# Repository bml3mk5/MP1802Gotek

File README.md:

# VFOインターフェース for MP-1802 / MP-1870 on 日立ベーシックマスターレベル３ / MB-S1

## フォルダ構成

    Board/ ......................... 基板設計(KiCAD Version 6)

-----
# VFO Interface for MP-1802 / MP-1870 on HITACH BASIC MASTER LEVEL3 / MB-S1

## Folders:

    Board/ ......................... Circuit board design(KiCAD Version 6)

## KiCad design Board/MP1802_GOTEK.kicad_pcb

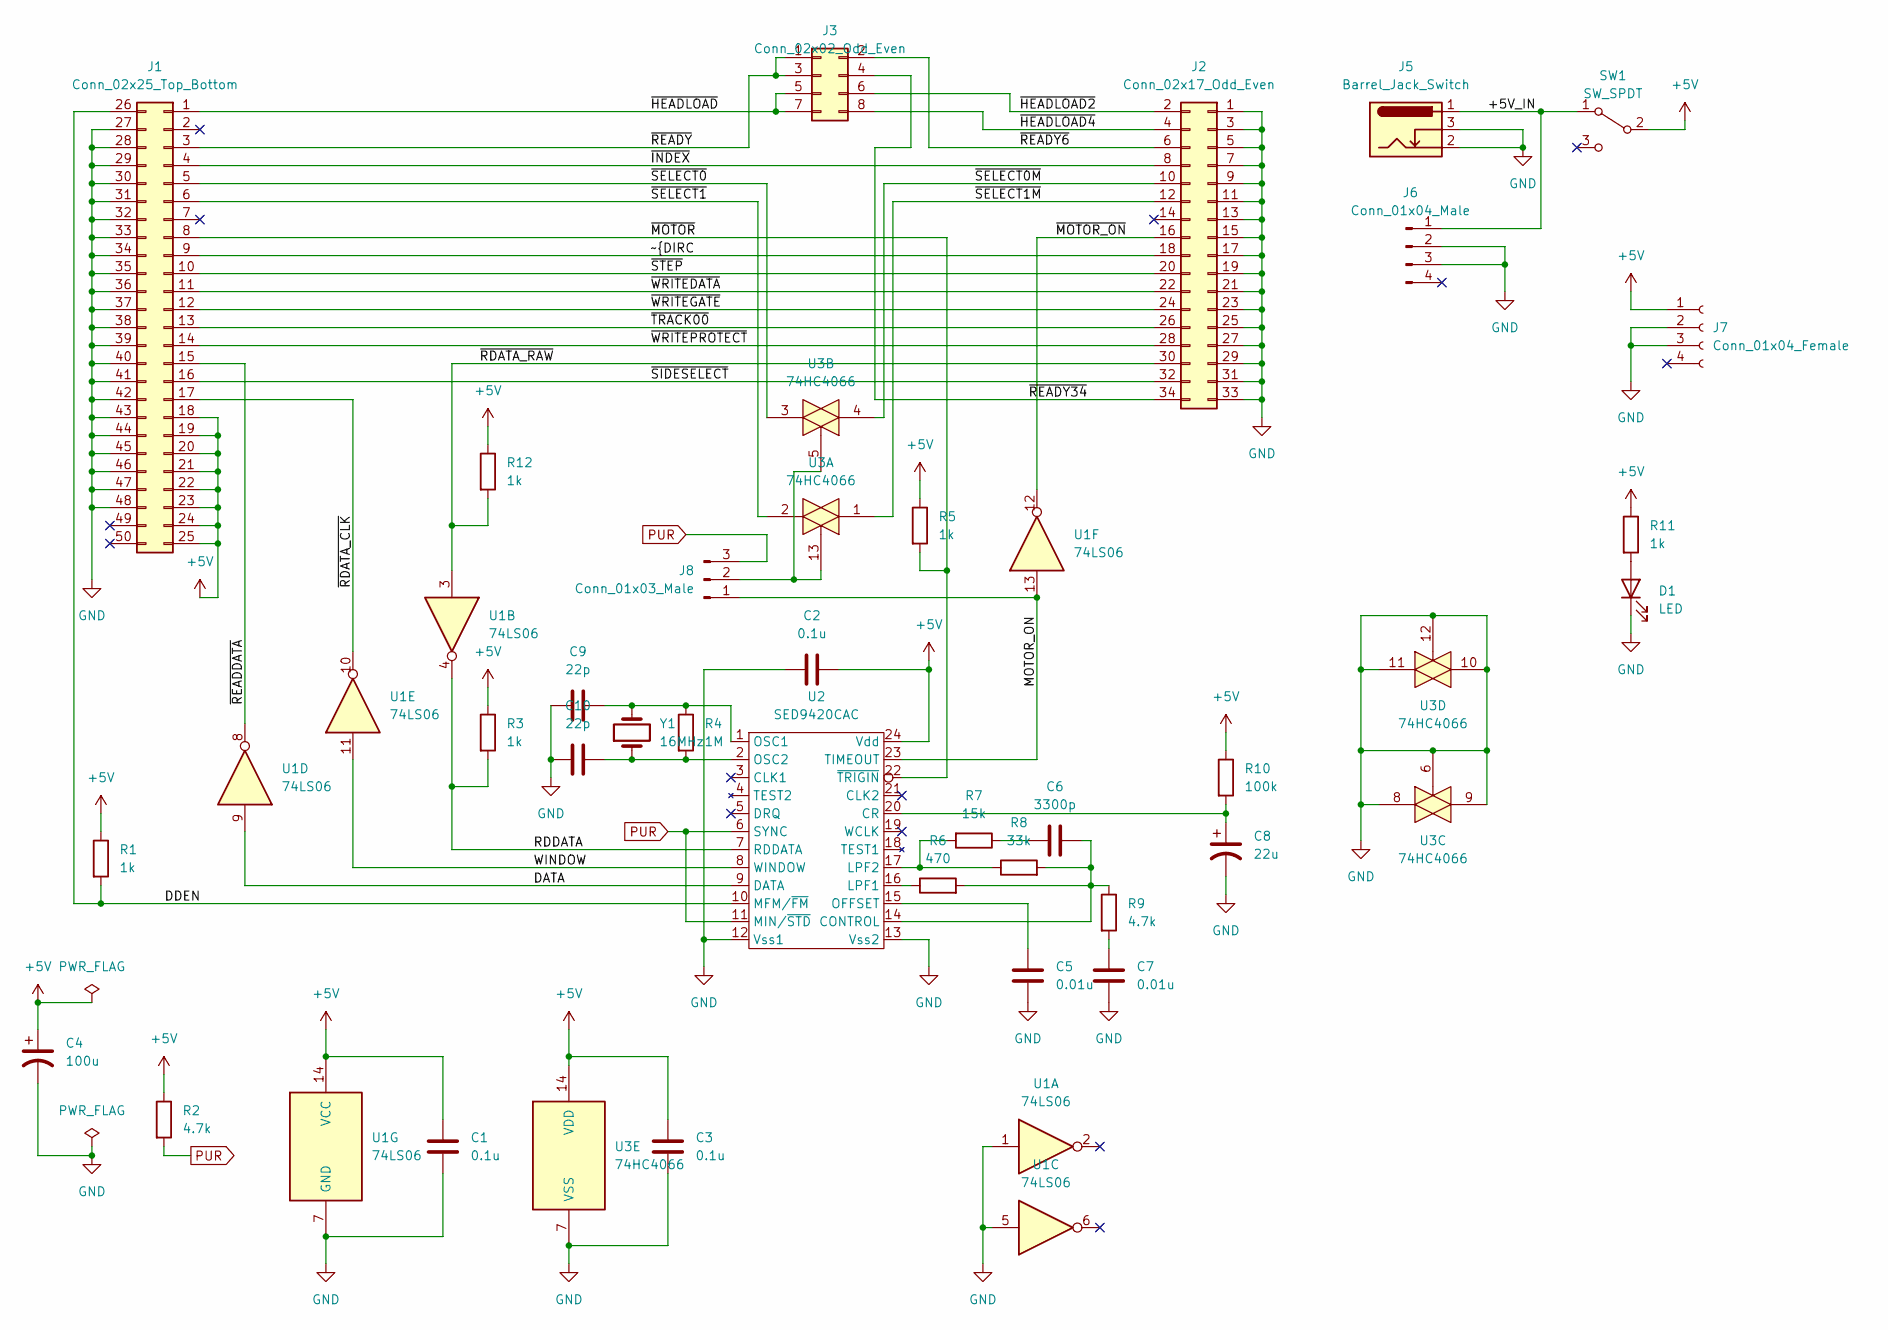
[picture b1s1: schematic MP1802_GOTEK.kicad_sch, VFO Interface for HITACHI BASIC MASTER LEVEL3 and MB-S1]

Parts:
C1, C2, C3: 0.1u; C_Disc_D3.0mm_W2.0mm_P2.50mm
C4: 100u; CP_Radial_D6.3mm_P2.50mm
C5, C7: 0.01u; C_Disc_D3.0mm_W2.0mm_P2.50mm
C6: 3300p; C_Disc_D3.0mm_W2.0mm_P2.50mm
C8: 22u; CP_Radial_D6.3mm_P2.50mm
C9, C10: 22p; C_Disc_D3.0mm_W2.0mm_P2.50mm
D1: LED; LED_D3.0mm
J1: Conn_02x25_Top_Bottom; YA_PinHeader_2x25_P2.54mm_Vertical
J2: Conn_02x17_Odd_Even; YA_PinHeader_2x17_P2.54mm_Vertical
J3: Conn_02x02_Odd_Even; PinHeader_2x04_P2.54mm_Vertical
J5: Barrel_Jack_Switch; YA_BarrelJack_CUI_PJ-102AH_Horizontal
J6: Conn_01x04_Male; PinHeader_1x04_P2.54mm_Horizontal
J7: Conn_01x04_Female; PinSocket_1x04_P2.54mm_Vertical
J8: Conn_01x03_Male; PinHeader_1x03_P2.54mm_Vertical
R1, R3, R5, R11, R12: 1k; R_Axial_DIN0207_L6.3mm_D2.5mm_P2.54mm_Vertical
R2: 4.7k; R_Axial_DIN0207_L6.3mm_D2.5mm_P2.54mm_Vertical
R4: 1M; R_Axial_DIN0207_L6.3mm_D2.5mm_P2.54mm_Vertical
R6: 470; R_Axial_DIN0207_L6.3mm_D2.5mm_P7.62mm_Horizontal
R7: 15k; R_Axial_DIN0207_L6.3mm_D2.5mm_P7.62mm_Horizontal
R8: 33k; R_Axial_DIN0207_L6.3mm_D2.5mm_P7.62mm_Horizontal
R9: 4.7k; R_Axial_DIN0207_L6.3mm_D2.5mm_P7.62mm_Horizontal
R10: 100k; R_Axial_DIN0207_L6.3mm_D2.5mm_P2.54mm_Vertical
SW1: SW_SPDT; SW_Switch_SS12D10_SPDT
U1: 74LS06; DIP-14_W7.62mm_Socket
U2: SED9420CAC; DIP-24_W15.24mm_Socket
U3: 74HC4066; DIP-14_W7.62mm_Socket
Y1: 16MHz; Crystal_HC18-U_Vertical

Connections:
+5V: C1.2, C2.2, C3.2, C4.1, J1.18, J1.19, J1.20, J1.21, J1.22, J1.23, J1.24, J1.25, J7.1, R1.1, R2.1, R3.1, R5.1, R10.1, R11.1, R12.1, SW1.2 (B), U1.14 (VCC), U2.24 (Vdd), U3.14 (VDD)
/+5V_IN: J5.1, J6.1, SW1.1 (A)
/DATA: U1.9, U2.9 (DATA)
/DDEN: J1.26, R1.2, U2.10 (MFM/~FM)
/MOTOR_ON: J8.1, U1.13, U2.23 (TIMEOUT)
/RDDATA: R3.2, U1.4, U2.7 (RDDATA)
/WINDOW: U1.11, U2.8 (WINDOW)
/~DIRC: J1.9, J2.18
/~HEADLOAD2: J2.2, J3.6
/~HEADLOAD4: J2.4, J3.8
/~HEADLOAD: J1.1, J3.5, J3.7
/~INDEX: J1.4, J2.8
/~MOTOR_ON: J2.16, U1.12
/~MOTOR: J1.8, R5.2, U2.22 (~TRIGIN)
/~RDATA_CLK: J1.17, U1.10
/~RDATA_RAW: J2.30, R12.2, U1.3
/~READDATA: J1.15, U1.8
/~READY6: J2.6, J3.2
/~READY34: J2.34, J3.4
/~READY: J1.3, J3.1, J3.3
/~SELECT0M: J2.10, U3.4
/~SELECT0: J1.5, U3.3
/~SELECT1M: J2.12, U3.1
/~SELECT1: J1.6, U3.2
/~SIDESELECT: J1.16, J2.32
/~STEP: J1.10, J2.20
/~TRACK00: J1.13, J2.26
/~WRITEDATA: J1.11, J2.22
/~WRITEGATE: J1.12, J2.24
/~WRITEPROTECT: J1.14, J2.28
GND: C1.1, C2.1, C3.1, C4.2, C5.1, C7.1, C8.2, C9.1, C10.1, D1.1 (K), J1.27, J1.28, J1.29, J1.30, J1.31, J1.32, J1.33, J1.34, J1.35, J1.36, J1.37, J1.38, J1.39, J1.40, J1.41, J1.42, J1.43, J1.44, J1.45, J1.46, J1.47, J1.48, J2.1, J2.3, J2.5, J2.7, J2.9, J2.11, J2.13, J2.15, J2.17, J2.19, J2.21, J2.23, J2.25, J2.27, J2.29, J2.31, J2.33, J5.2, J5.3, J6.2, J6.3, J7.2, J7.3, U1.1, U1.5, U1.7 (GND), U2.12 (Vss1), U2.13 (Vss2), U3.6, U3.7 (VSS), U3.8, U3.9, U3.10, U3.11, U3.12
unnamed: C5.2, U2.15 (OFFSET)
unnamed: C6.1, R7.1
unnamed: C6.2, R6.2, R8.2, R9.1, U2.14 (CONTROL)
unnamed: C7.2, R9.2
unnamed: C8.1, R10.2, U2.20 (CR)
unnamed: C9.2, R4.1, U2.1 (OSC1), Y1.2
unnamed: C10.2, R4.2, U2.2 (OSC2), Y1.1
unnamed: D1.2 (A), R11.2
unnamed: J8.2, U3.5, U3.13
unnamed: R6.1, U2.16 (LPF1)
unnamed: R7.2, R8.1, U2.17 (LPF2)
PUR: J8.3, R2.2, U2.6 (SYNC), U2.11 (MIN/~STD)

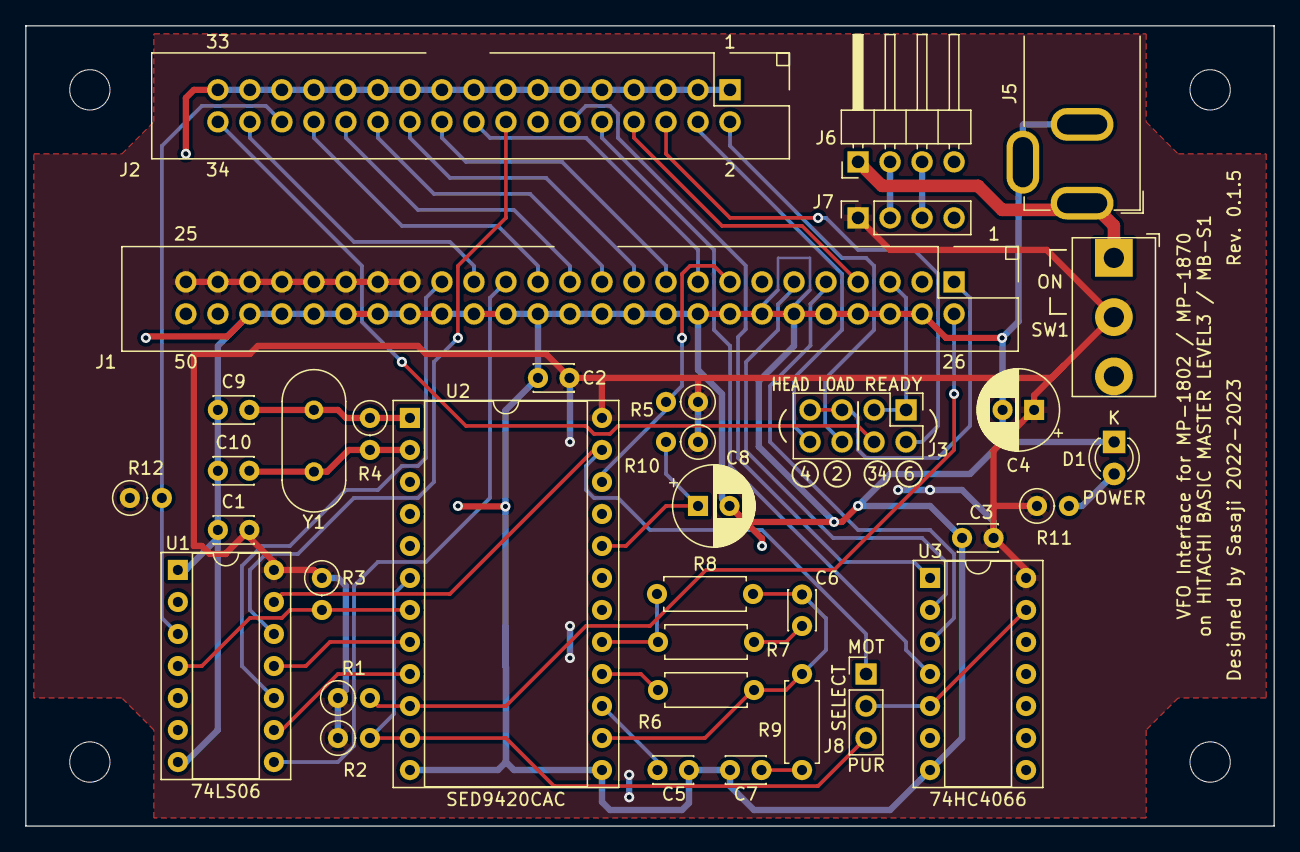
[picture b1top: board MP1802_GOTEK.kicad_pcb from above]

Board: 2 copper layers, 99.1 x 63.5 mm, 35 parts (0 on the bottom side), 43 nets.

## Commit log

2023-11-18 Version 0.1.2
2023-11-18 Revision 0.1.5
